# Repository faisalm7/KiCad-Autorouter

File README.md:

# Copperpath — KiCad-Autorouter

A local, open-source KiCad design assistant built around Freerouting. Ordinary controls support routing and constrained selected-component placement without an AI account. Deterministic tools enforce supported constraints, preserve protected content and validate separate candidates. An optional copilot can propose settings; it cannot run, approve or accept a board. [Product strategy](docs/product-strategy.md).

**Experimental software.** The installed workspace let an operator select two resistors, revise the routing time in the Request pane, and review the checked move of R2. It routed three approved nets on the retained MIT PushButtonLed design. The export and readback found zero opens and zero blockers, kept 13 protected tracks, and retained all seven inherited warnings. The local parser supports bounded placement wording without an AI account. At laptop size the board and conversation stay beside the review. [Use direct requests](docs/direct-conversation-journey.md) · [Installed walkthrough](evidence/product-direct-conversation-001.json) · [Current state](STATUS.md)

An earlier live copilot suggestion led to a separate checked export through explicit approval and ordinary controls. Rejection, cancellation, stale-input refusal and checked opening have their own build-specific evidence. [Conversation to delivery](evidence/product-workspace-hosted-engineering-001.json) · [101 safety controls](evidence/product101-GUI124-core-001.json).

The retained **094 / GUI118 licensed-task reference** has its own [delivery](evidence/runtime094-licensed-placement-delivery-001.json) and [GUI evidence](evidence/runtime094-GUI118-core-001.json). Historical failures remain recorded. No general routing superiority or measured human cleanup gain is established.

[Start here](START_HERE.md) · [Saved-project workflow](docs/quickstart.md) · [Installation and advanced CLI](docs/install-existing.md) · [Current state](STATUS.md) · [Requirements](REQUIREMENTS.md).

Use your installed launcher and your own complete saved project. Inspect the exact source, choose supported settings, preview, run, review every finding, and explicitly accept or reject. Fresh export creates a separately validated project; it never applies changes to an open source board. Cancel requests cleanup and revokes results. Source, settings or editor-sidecar changes require fresh checks.

Placement remains limited to its explicit geometry and copper policies. Unselected/fixed components stay fixed; orientation and side changes are unsupported. The opt-in target-region initializer covers two independent selected parts in its specific Native source-baseline scope, not general repair of an invalid or unplaced board. Unsupported requests refuse. The [small owned example and preset](examples/owned-placement-routing/README.md) make the walkthrough available without the research archive. Freshly inspect your own complete saved input. Previous095export,100saved-Default and other failures remain recorded; source-only changes do not inherit graphical qualification.

First setup and Finder launch have been checked on the same Mac. Standalone and independent installation, Windows Native workflows, general live edits, full current and off-Mac recovery, and human and physical review remain open. One isolated KiCad 10.0.8 example passed a checked move and native Undo. Normal routing needs no model endpoint, network, Git or research archive. The [older synthetic screen](evidence/copilot-screen097-completed-001.json) exposes an application-contract defect and qualifies neither model. After the shared correction, the [completed 20-call confirmation](evidence/copilot-confirmation098-completed-001.json) records Sol 10/10 and Luna 8/10 targeted intent decisions. The overall both-profile gate failed. The [first live pilot](evidence/copilot101-owned-live-failure-001.json) remains failed. The separately approved 102 attempt completed at $0.0058445 usage-priced cost and 6.40 seconds client time. Both attempts together cost $0.011689 and the earlier unknown reservation remains. Sol/medium stays opt-in with explicit data and cost consent and independent engineering approvals. [Editor scope](evidence/live-editor-1008-direct-002.json) · [Setup](evidence/product-direct-first-setup-and-keyboard-002.json).

Original code and owned fixtures are GPL-3.0-or-later. Reused MIT placement modules retain their notice; other material keeps its separate [rights and provenance](docs/data-provenance.md). Freerouting remains the primary routing engine. No formal package or release is claimed.

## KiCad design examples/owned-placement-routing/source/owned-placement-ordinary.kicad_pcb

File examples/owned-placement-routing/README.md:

# Owned placement-and-routing example

This small GPL-3.0-or-later development board demonstrates the ordinary controls without an AI account. It is a software-test design, not an electrically reviewed product. Its primary PCB, project and complete schematic bytes match the recorded [live application task](../../evidence/copilot102-owned-live-delivery-001.json).

1. Open `source/owned-placement-ordinary.kicad_pro` through your installed isolated KiCad launcher, open PCB Editor and click the Autorouter toolbar icon.
2. Save and close the PCB/schematic editors, then choose **File → Close Project** in KiCad manager. In the assistant, choose the exact saved PCB and a separate output folder.
3. Open **Place components…**, inspect the project and use **Load settings…** to select this folder’s `settings.json`. Review J1/J2 as movable, J3–J6 fixed, the 14–22 × 8–13 mm area, and the explicit affected-net rebuild policy. KEEP and locked/unrelated copper remain protected. The outside-area initializer is explicitly experimental.
4. Choose **Find alternatives**, inspect the diagram and findings, and acknowledge the exact moves and copper plan. The current build returns to **Board** and enables **Validate placement** once the preview renders. On older builds, select **Board** if needed. Validate and continue to the guarded routing settings.
5. Preview, route, create the review and inspect every finding/layer. Explicitly accept or reject. **Fresh export** runs new checks and creates a separate project. The inherited 0.7 mm silkscreen-text warning against a 0.8 mm minimum remains; success is not whole-project DRC cleanliness or electrical approval.

For the optional, separately consented copilot interface, select the same visible controls and ask:

> Keep the fixed components and protected trace unchanged, place these two components inside this region, then route their approved connections.

Review its visible plan before using it to find alternatives. Model/data/cost consent and engineering approvals are separate; no model endpoint, account or spending permission is supplied by this example. Do not reuse an old receipt as approval.

The recorded run also retained optional local UI settings and a KiCad-generated backup. Those are omitted from this portable example and remain in the local evidence. Its complete file-set identity must therefore be captured afresh after opening/saving. No new Native run or model result is claimed merely from publishing these same primary design bytes. This family is exposed development data, never an untouched confirmation case.

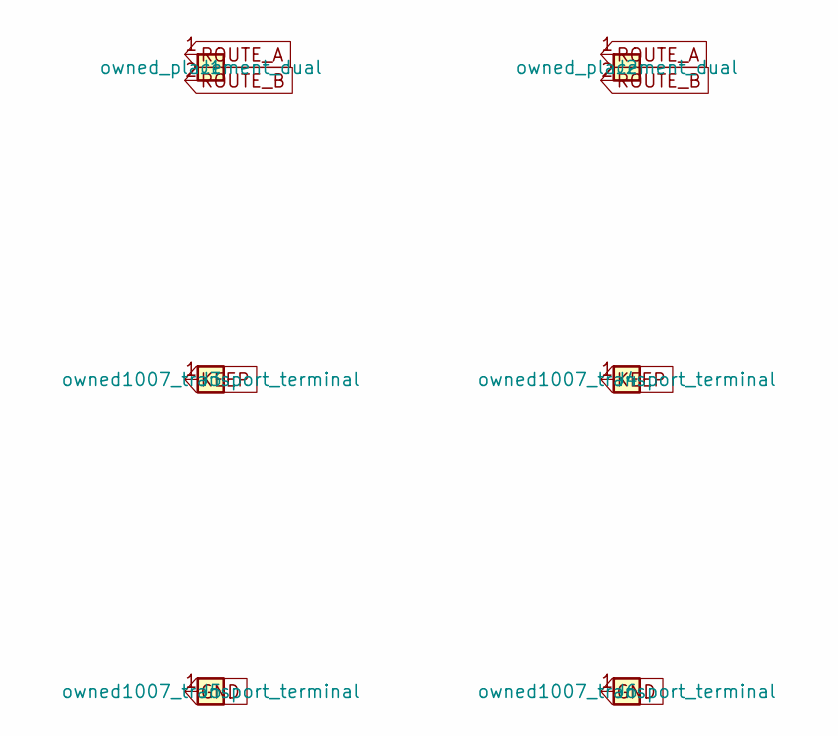
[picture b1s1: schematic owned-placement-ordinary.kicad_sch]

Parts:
J1, J2: owned_placement_dual
J3, J4, J5, J6: owned1007_transport_terminal

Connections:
GND: J5.1, J6.1
KEEP: J3.1, J4.1
ROUTE_A: J1.1, J2.1
ROUTE_B: J1.2, J2.2

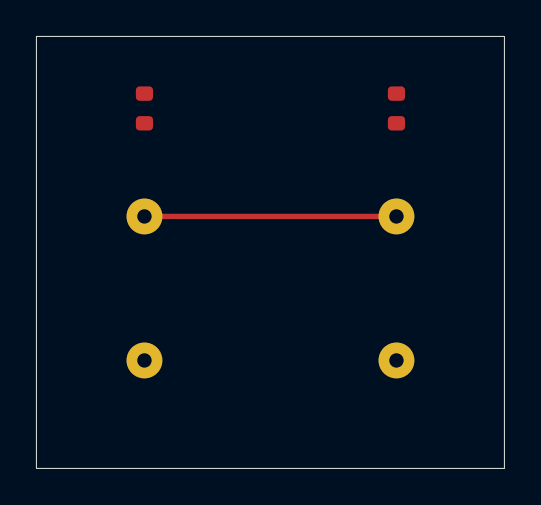
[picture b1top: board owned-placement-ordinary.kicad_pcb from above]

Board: 2 copper layers, 26.0 x 24.0 mm, 6 parts (0 on the bottom side), 4 nets.

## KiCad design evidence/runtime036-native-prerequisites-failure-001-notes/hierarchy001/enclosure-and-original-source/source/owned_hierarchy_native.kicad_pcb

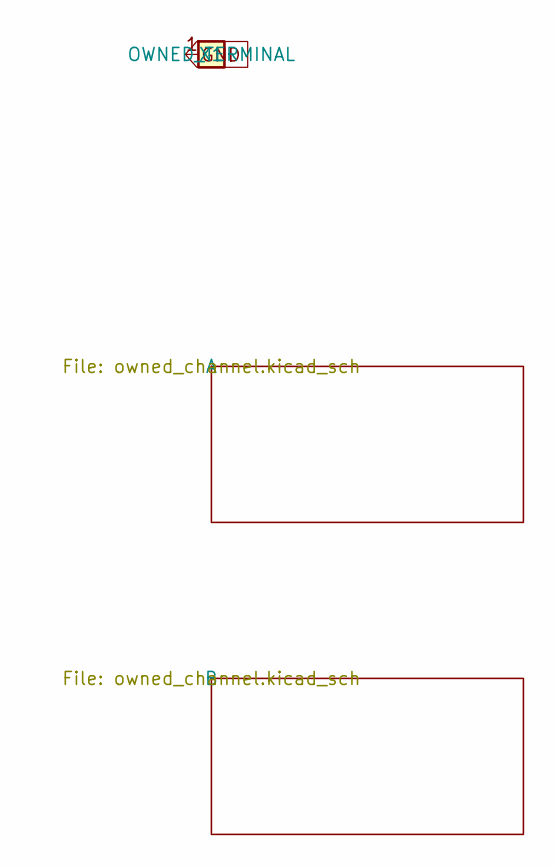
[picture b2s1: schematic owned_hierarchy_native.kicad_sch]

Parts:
X1: OWNED_TERMINAL; owned_hierarchy_terminal

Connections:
GND: X1.1; also elsewhere on the board

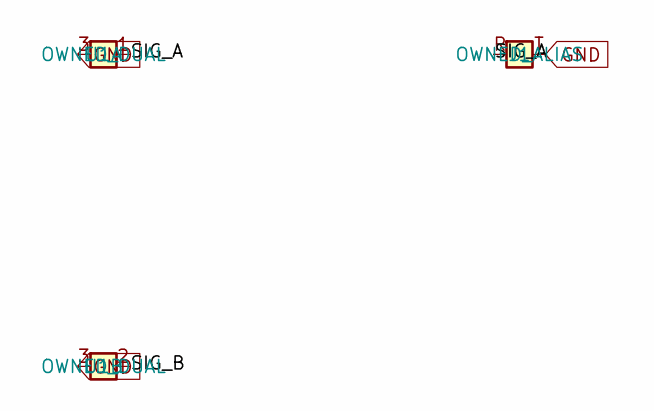
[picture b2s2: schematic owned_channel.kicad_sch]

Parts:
J1: OWNED_ALIAS; owned_hierarchy_alias
U1: OWNED_DUAL; owned_hierarchy_dual

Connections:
/A/SIG_A: J1.R, U1.1
/A/SIG_B: U1.2
GND: J1.T, U1.3; also elsewhere on the board

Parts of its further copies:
J2: OWNED_ALIAS; owned_hierarchy_alias
U2: OWNED_DUAL; owned_hierarchy_dual

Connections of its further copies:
/B/SIG_A: J2.R, U2.1
/B/SIG_B: U2.2
GND: J2.T, U2.3; also elsewhere on the board

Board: 2 copper layers, 5 parts (0 on the bottom side), 3 nets, no tracks yet.

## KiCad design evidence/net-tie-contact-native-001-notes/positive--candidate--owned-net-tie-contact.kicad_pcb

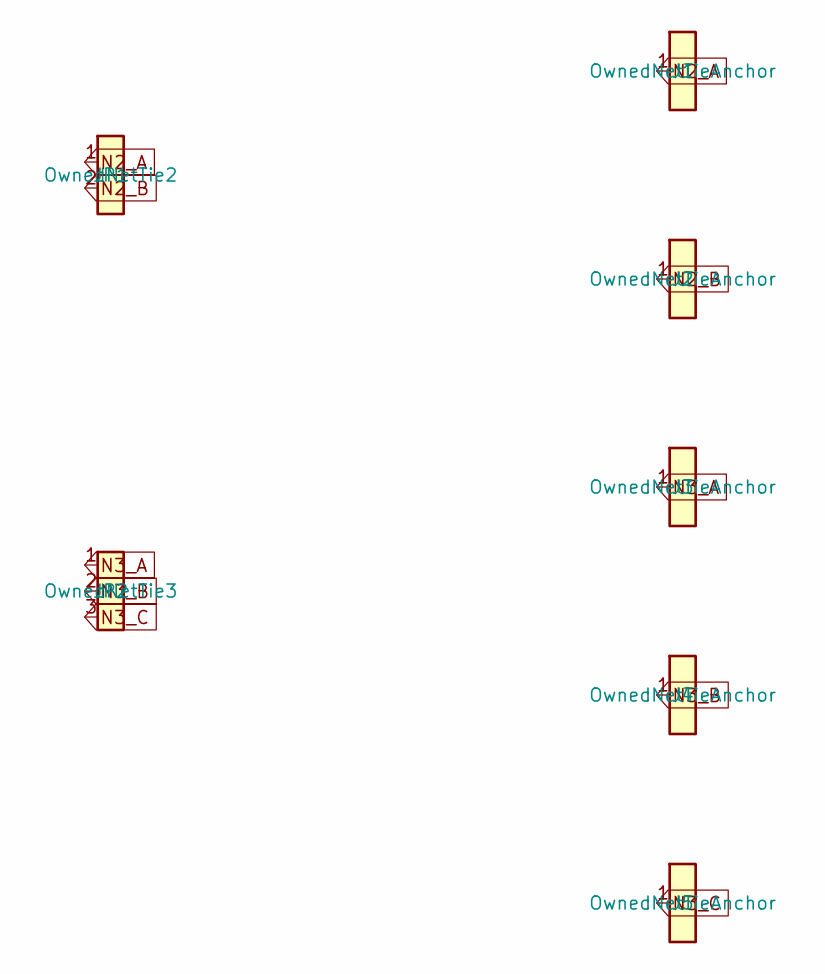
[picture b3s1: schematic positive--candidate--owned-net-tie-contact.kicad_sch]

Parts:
J1, J2, J3, J4, J5: OwnedNetTieAnchor
JP1: OwnedNetTie2
JP2: OwnedNetTie3

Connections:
N2_A: J1.1, JP1.1
N2_B: J2.1, JP1.2
N3_A: J3.1, JP2.1
N3_B: J4.1, JP2.2
N3_C: J5.1, JP2.3

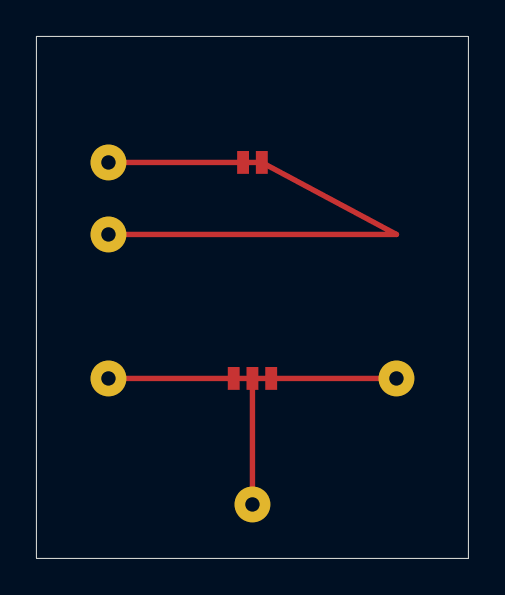
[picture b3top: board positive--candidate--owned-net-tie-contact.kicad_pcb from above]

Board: 2 copper layers, 24.0 x 29.0 mm, 7 parts (0 on the bottom side), 5 nets.
